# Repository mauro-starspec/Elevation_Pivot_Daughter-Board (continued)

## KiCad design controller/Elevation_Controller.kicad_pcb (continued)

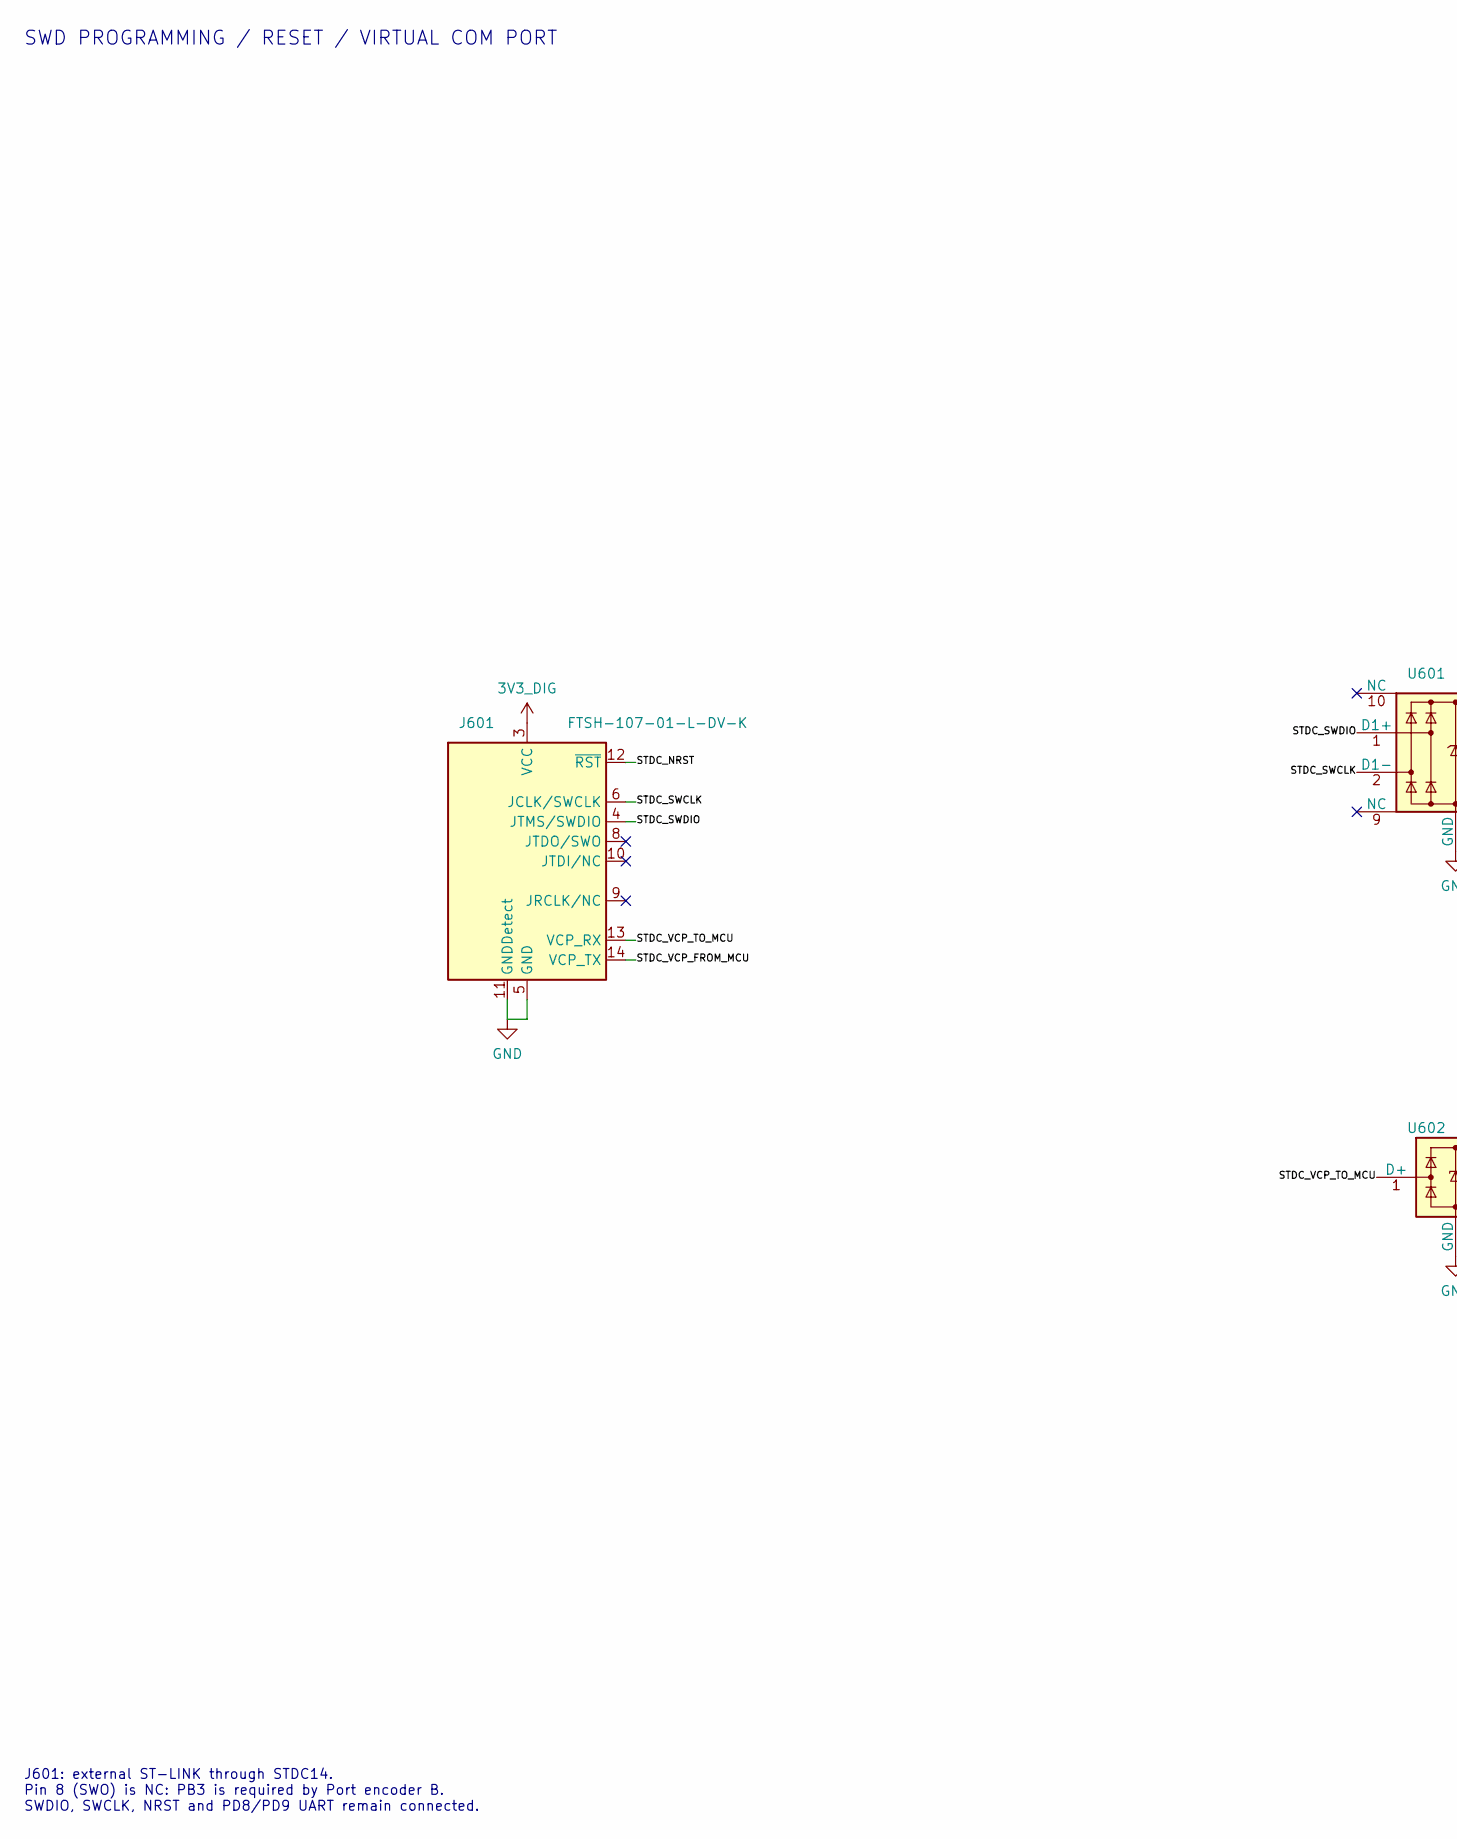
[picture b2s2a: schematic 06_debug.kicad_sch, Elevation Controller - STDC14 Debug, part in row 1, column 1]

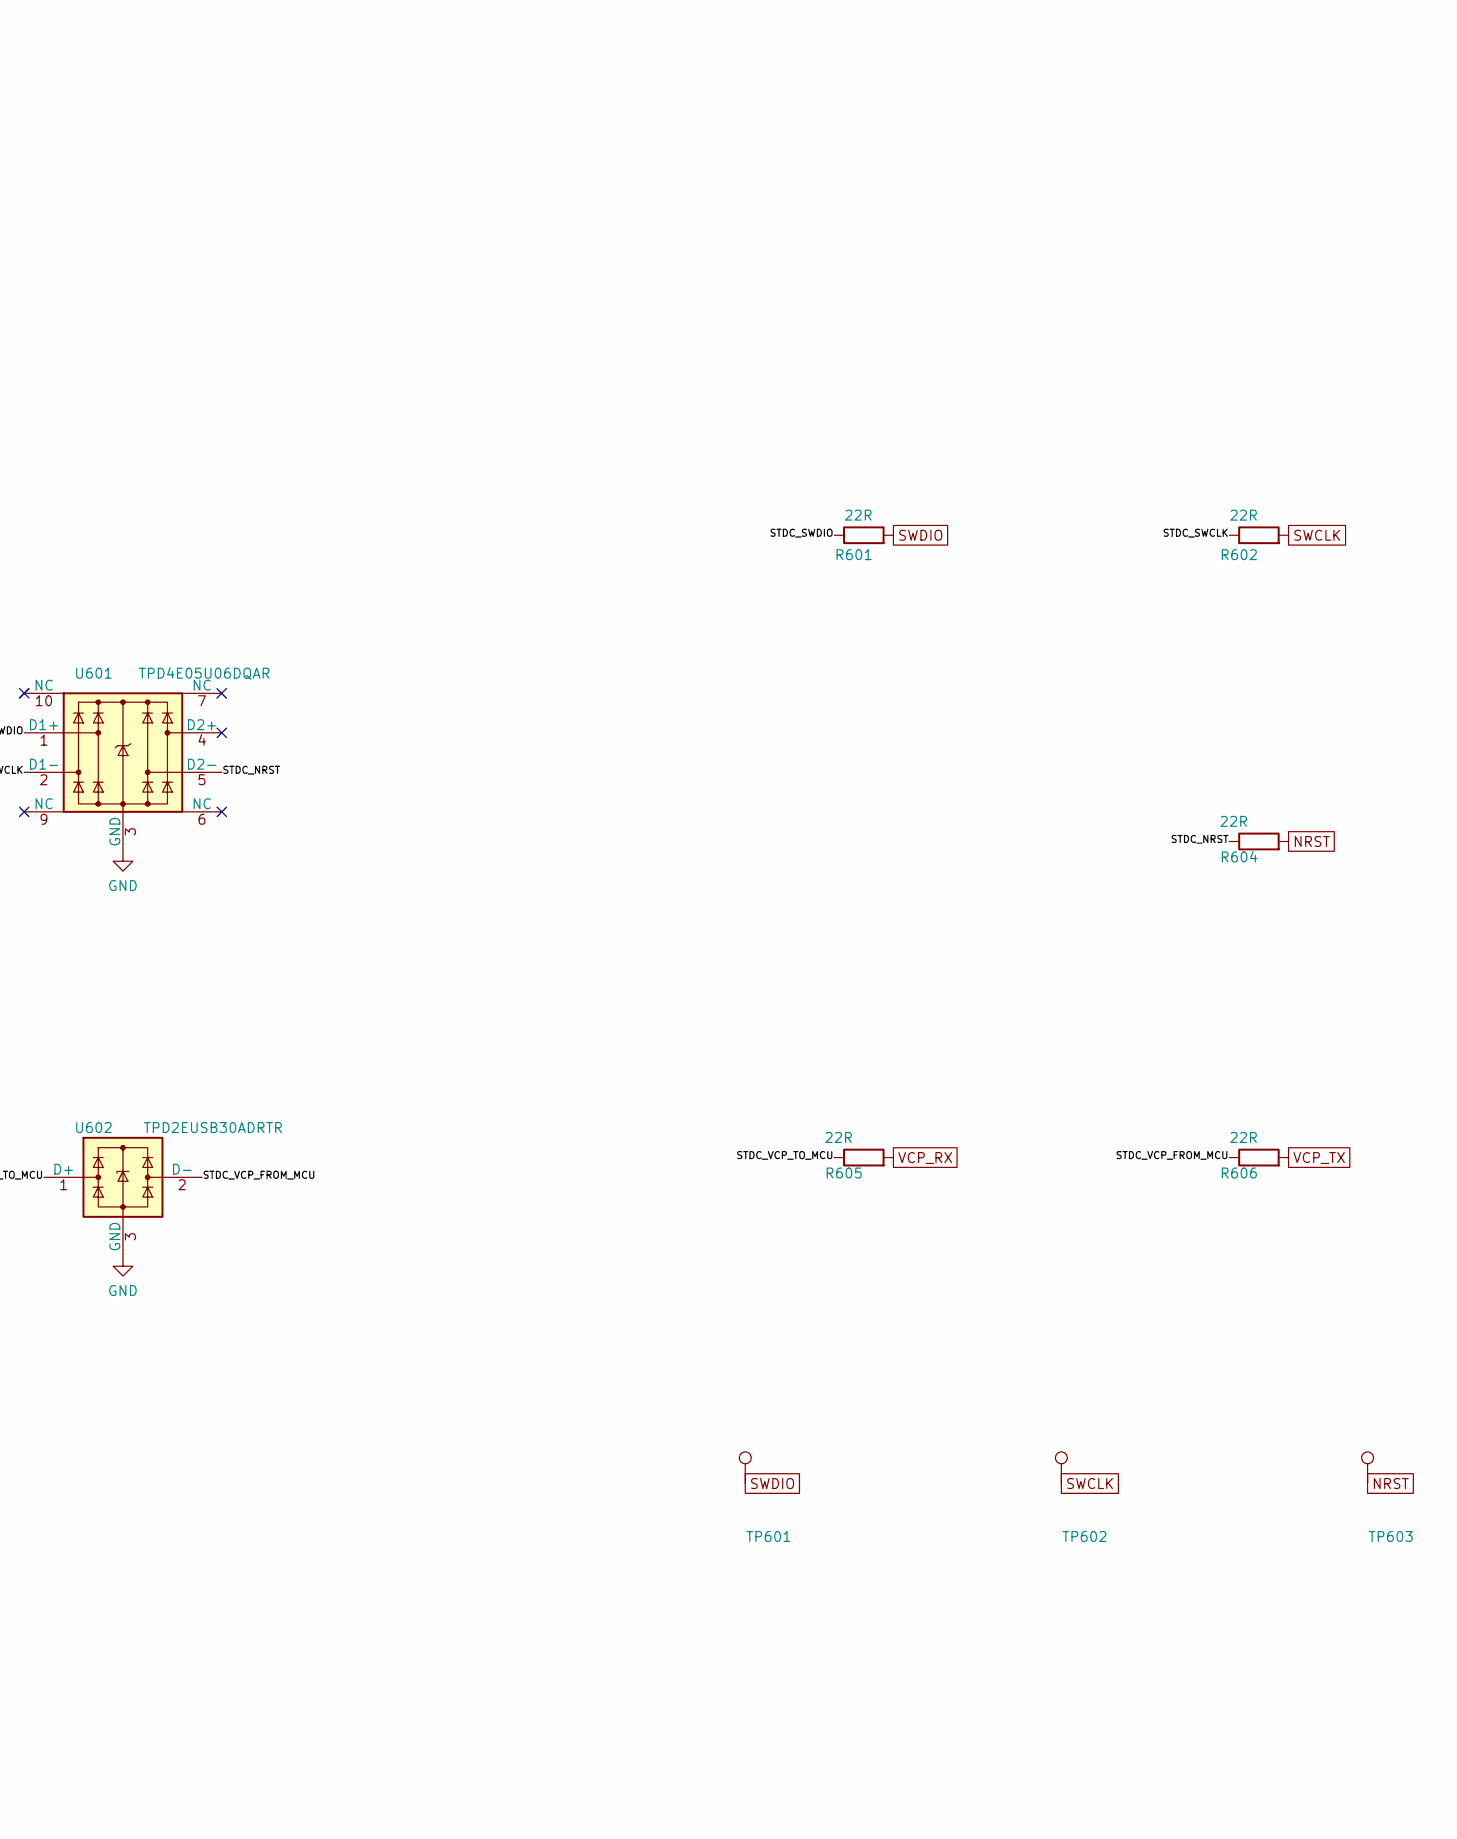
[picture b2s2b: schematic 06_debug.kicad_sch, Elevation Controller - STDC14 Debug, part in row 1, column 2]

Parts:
J601: FTSH-107-01-L-DV-K; Samtec_FTSH-107-01-L-DV-K; MPN FTSH-107-01-L-DV-K; LCSC Part # C5307809
R601, R602, R604, R605, R606: 22R; R_0805_2012Metric; MPN CRCW080522R0FKEA; LCSC Part # C844832
TP601: SWDIO; TestPoint_Pad_D2.0mm; MPN N/A; LCSC Part # N/A
TP602: SWCLK; TestPoint_Pad_D2.0mm; MPN N/A; LCSC Part # N/A
TP603: NRST; TestPoint_Pad_D2.0mm; MPN N/A; LCSC Part # N/A
U601: TPD4E05U06DQAR; USON-10_2.5x1.0mm_P0.5mm; MPN TPD4E05U06DQAR; LCSC Part # C22390021
U602: TPD2EUSB30ADRTR; Texas_DRT-3; MPN TPD2EUSB30ADRTR; LCSC Part # C94934

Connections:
3V3_DIG: J601.3 (VCC); also elsewhere on the board
/SWD and VCP/STDC_NRST: J601.12 (~RST), R604.1, U601.5 (D2-)
/SWD and VCP/STDC_SWCLK: J601.6 (JCLK/SWCLK), R602.1, U601.2 (D1-)
/SWD and VCP/STDC_SWDIO: J601.4 (JTMS/SWDIO), R601.1, U601.1 (D1+)
/SWD and VCP/STDC_VCP_FROM_MCU: J601.14 (VCP_TX), R606.1, U602.2 (D-)
/SWD and VCP/STDC_VCP_TO_MCU: J601.13 (VCP_RX), R605.1, U602.1 (D+)
GND: J601.5 (GND), J601.7 (GND), J601.11 (GNDDetect), U601.3 (GND), U601.8 (GND), U602.3 (GND); also elsewhere on the board
NRST: R604.2, TP603.1; also elsewhere on the board
SWCLK: R602.2, TP602.1; also elsewhere on the board
SWDIO: R601.2, TP601.1; also elsewhere on the board
VCP_RX: R605.2; also elsewhere on the board
VCP_TX: R606.2; also elsewhere on the board

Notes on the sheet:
J601: external ST-LINK through STDC14. Pin 8 (SWO) is NC: PB3 is required by Port encoder B. SWDIO, SWCLK, NRST and PD8/PD9 UART remain connected.
SWD PROGRAMMING / RESET / VIRTUAL COM PORT

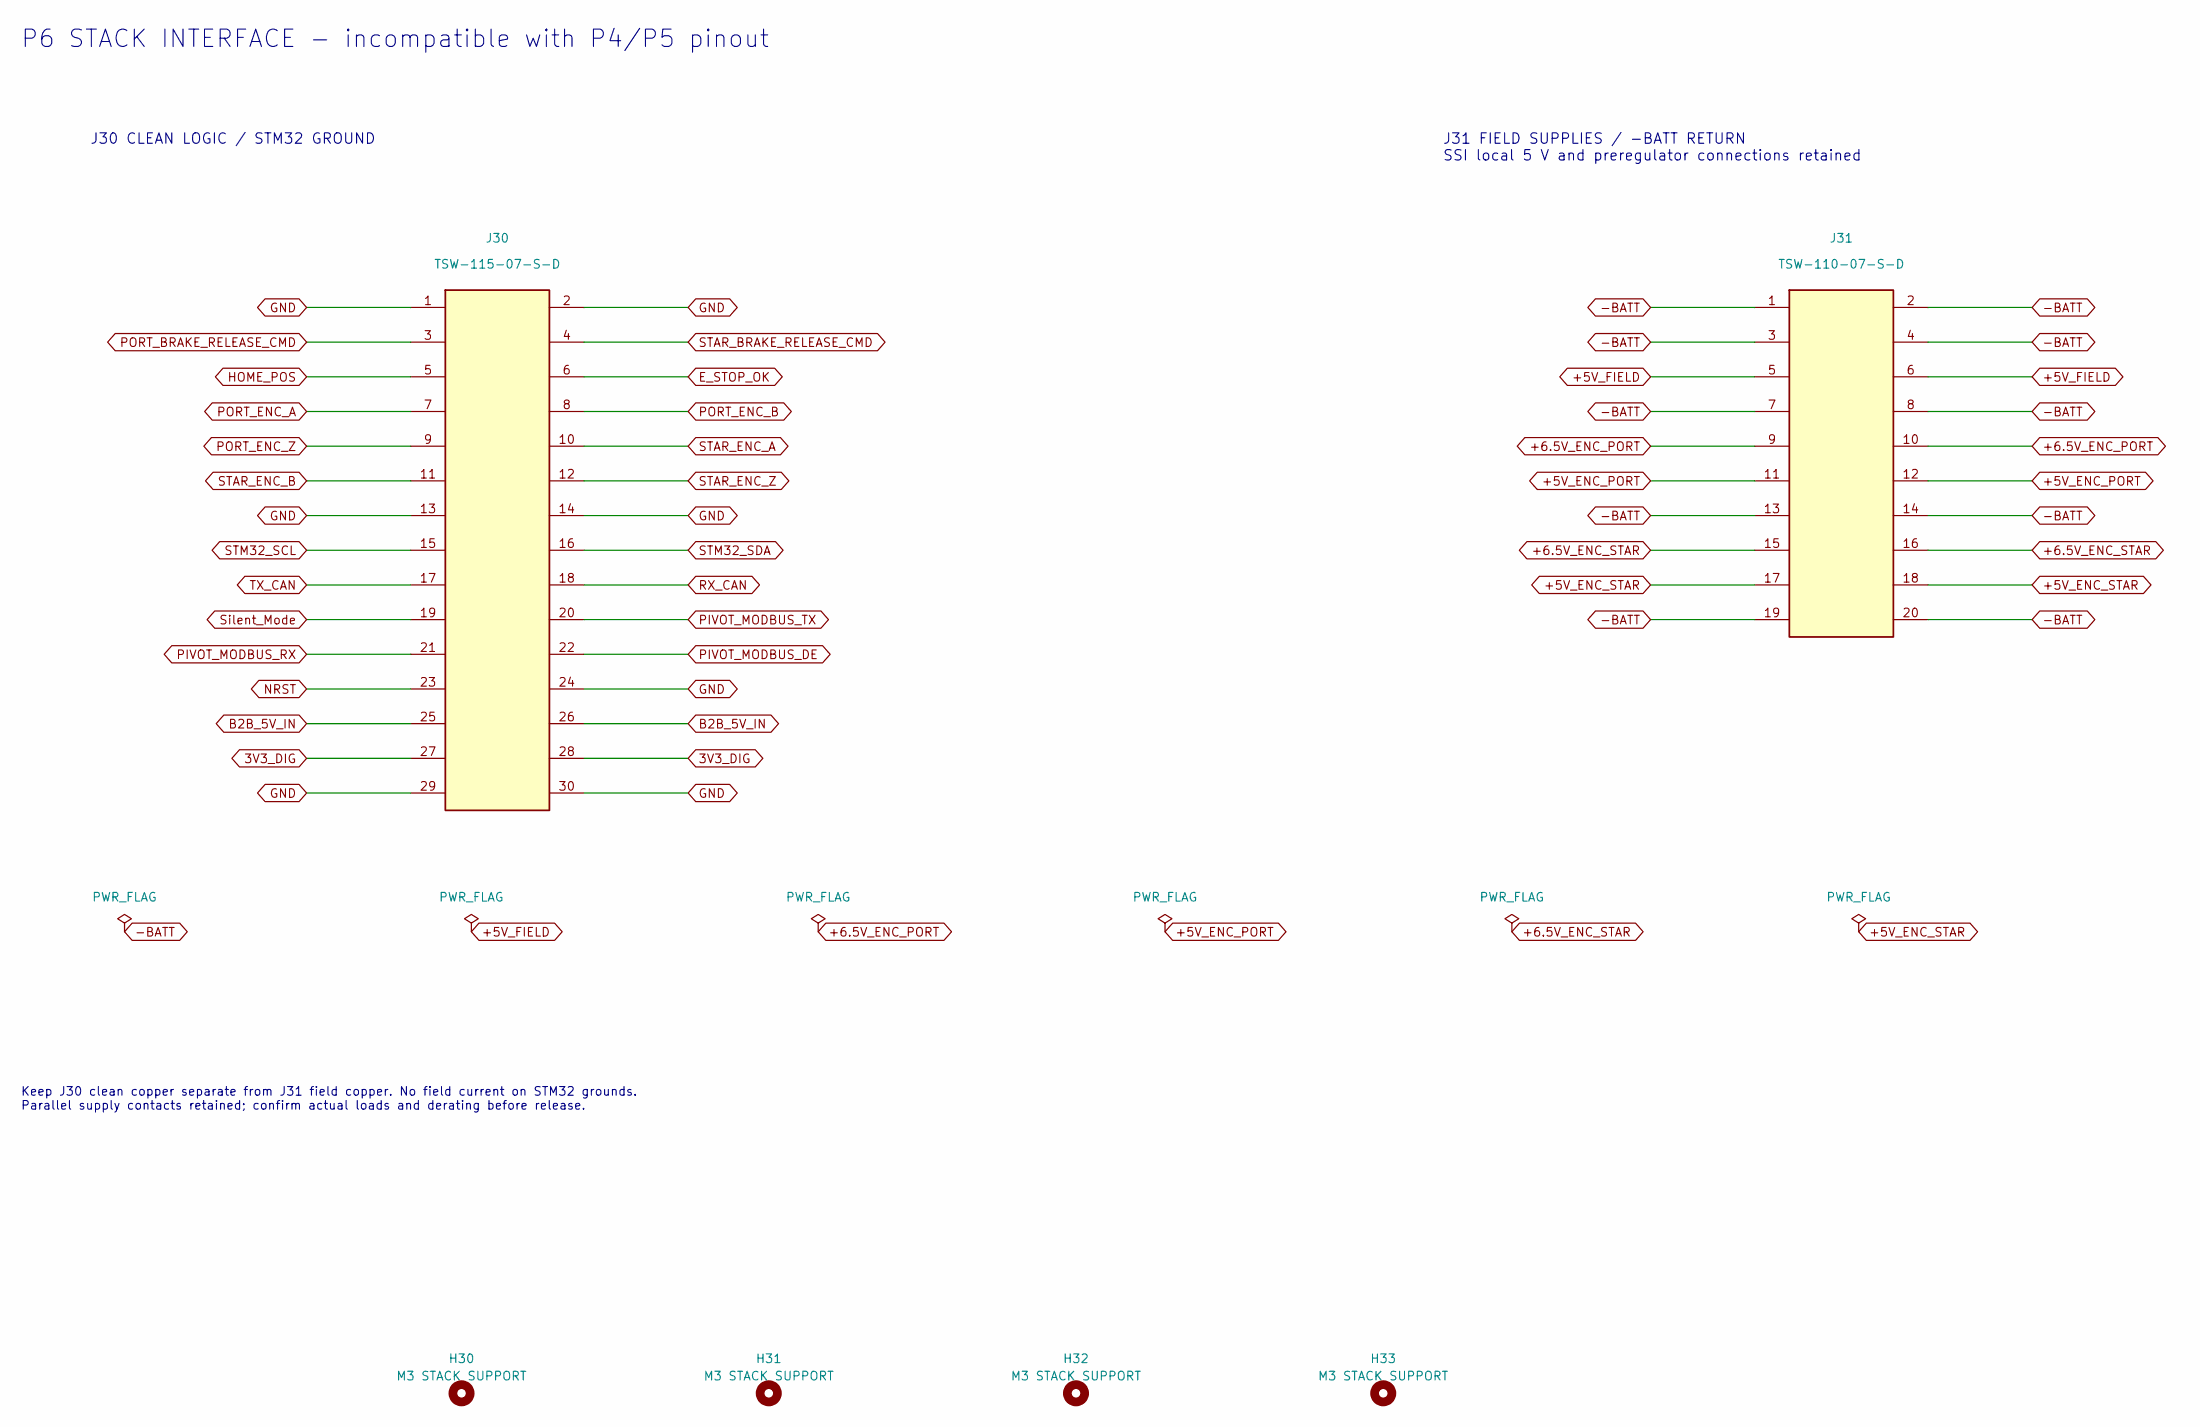
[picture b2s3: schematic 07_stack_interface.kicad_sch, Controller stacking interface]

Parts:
H30, H31, H32, H33: M3 STACK SUPPORT; MountingHole_3.2mm_M3; MPN N/A; JLCPCB Status N/A
J30: TSW-115-07-S-D; Samtec_TSW-115-07-S-D; MPN TSW-115-07-S-D; JLCPCB Status No verified JLCPCB ID; source or consign
J31: TSW-110-07-S-D; Samtec_TSW-110-07-S-D; MPN TSW-110-07-S-D; JLCPCB Status No verified JLCPCB ID; source or consign

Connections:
3V3_DIG: J30.27, J30.28; also elsewhere on the board
+5V_ENC_PORT: J31.11, J31.12; also elsewhere on the board
+5V_ENC_STAR: J31.17, J31.18; also elsewhere on the board
+5V_FIELD: J31.5, J31.6; also elsewhere on the board
+6.5V_ENC_PORT: J31.9, J31.10; also elsewhere on the board
+6.5V_ENC_STAR: J31.15, J31.16; also elsewhere on the board
-BATT: J31.1, J31.2, J31.3, J31.4, J31.7, J31.8, J31.13, J31.14, J31.19, J31.20; also elsewhere on the board
B2B_5V_IN: J30.25, J30.26; also elsewhere on the board
E_STOP_OK: J30.6; also elsewhere on the board
GND: J30.1, J30.2, J30.13, J30.14, J30.24, J30.29, J30.30; also elsewhere on the board
HOME_POS: J30.5; also elsewhere on the board
NRST: J30.23; also elsewhere on the board
PIVOT_MODBUS_DE: J30.22; also elsewhere on the board
PIVOT_MODBUS_RX: J30.21; also elsewhere on the board
PIVOT_MODBUS_TX: J30.20; also elsewhere on the board
PORT_BRAKE_RELEASE_CMD: J30.3; also elsewhere on the board
PORT_ENC_A: J30.7; also elsewhere on the board
PORT_ENC_B: J30.8; also elsewhere on the board
PORT_ENC_Z: J30.9; also elsewhere on the board
RX_CAN: J30.18; also elsewhere on the board
STAR_BRAKE_RELEASE_CMD: J30.4; also elsewhere on the board
STAR_ENC_A: J30.10; also elsewhere on the board
STAR_ENC_B: J30.11; also elsewhere on the board
STAR_ENC_Z: J30.12; also elsewhere on the board
STM32_SCL: J30.15; also elsewhere on the board
STM32_SDA: J30.16; also elsewhere on the board
Silent_Mode: J30.19; also elsewhere on the board
TX_CAN: J30.17; also elsewhere on the board

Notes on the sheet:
P6 STACK INTERFACE - incompatible with P4/P5 pinout
J30 CLEAN LOGIC / STM32 GROUND
J31 FIELD SUPPLIES / -BATT RETURN SSI local 5 V and preregulator connections retained
Keep J30 clean copper separate from J31 field copper. No field current on STM32 grounds. Parallel supply contacts retained; confirm actual loads and derating before release.

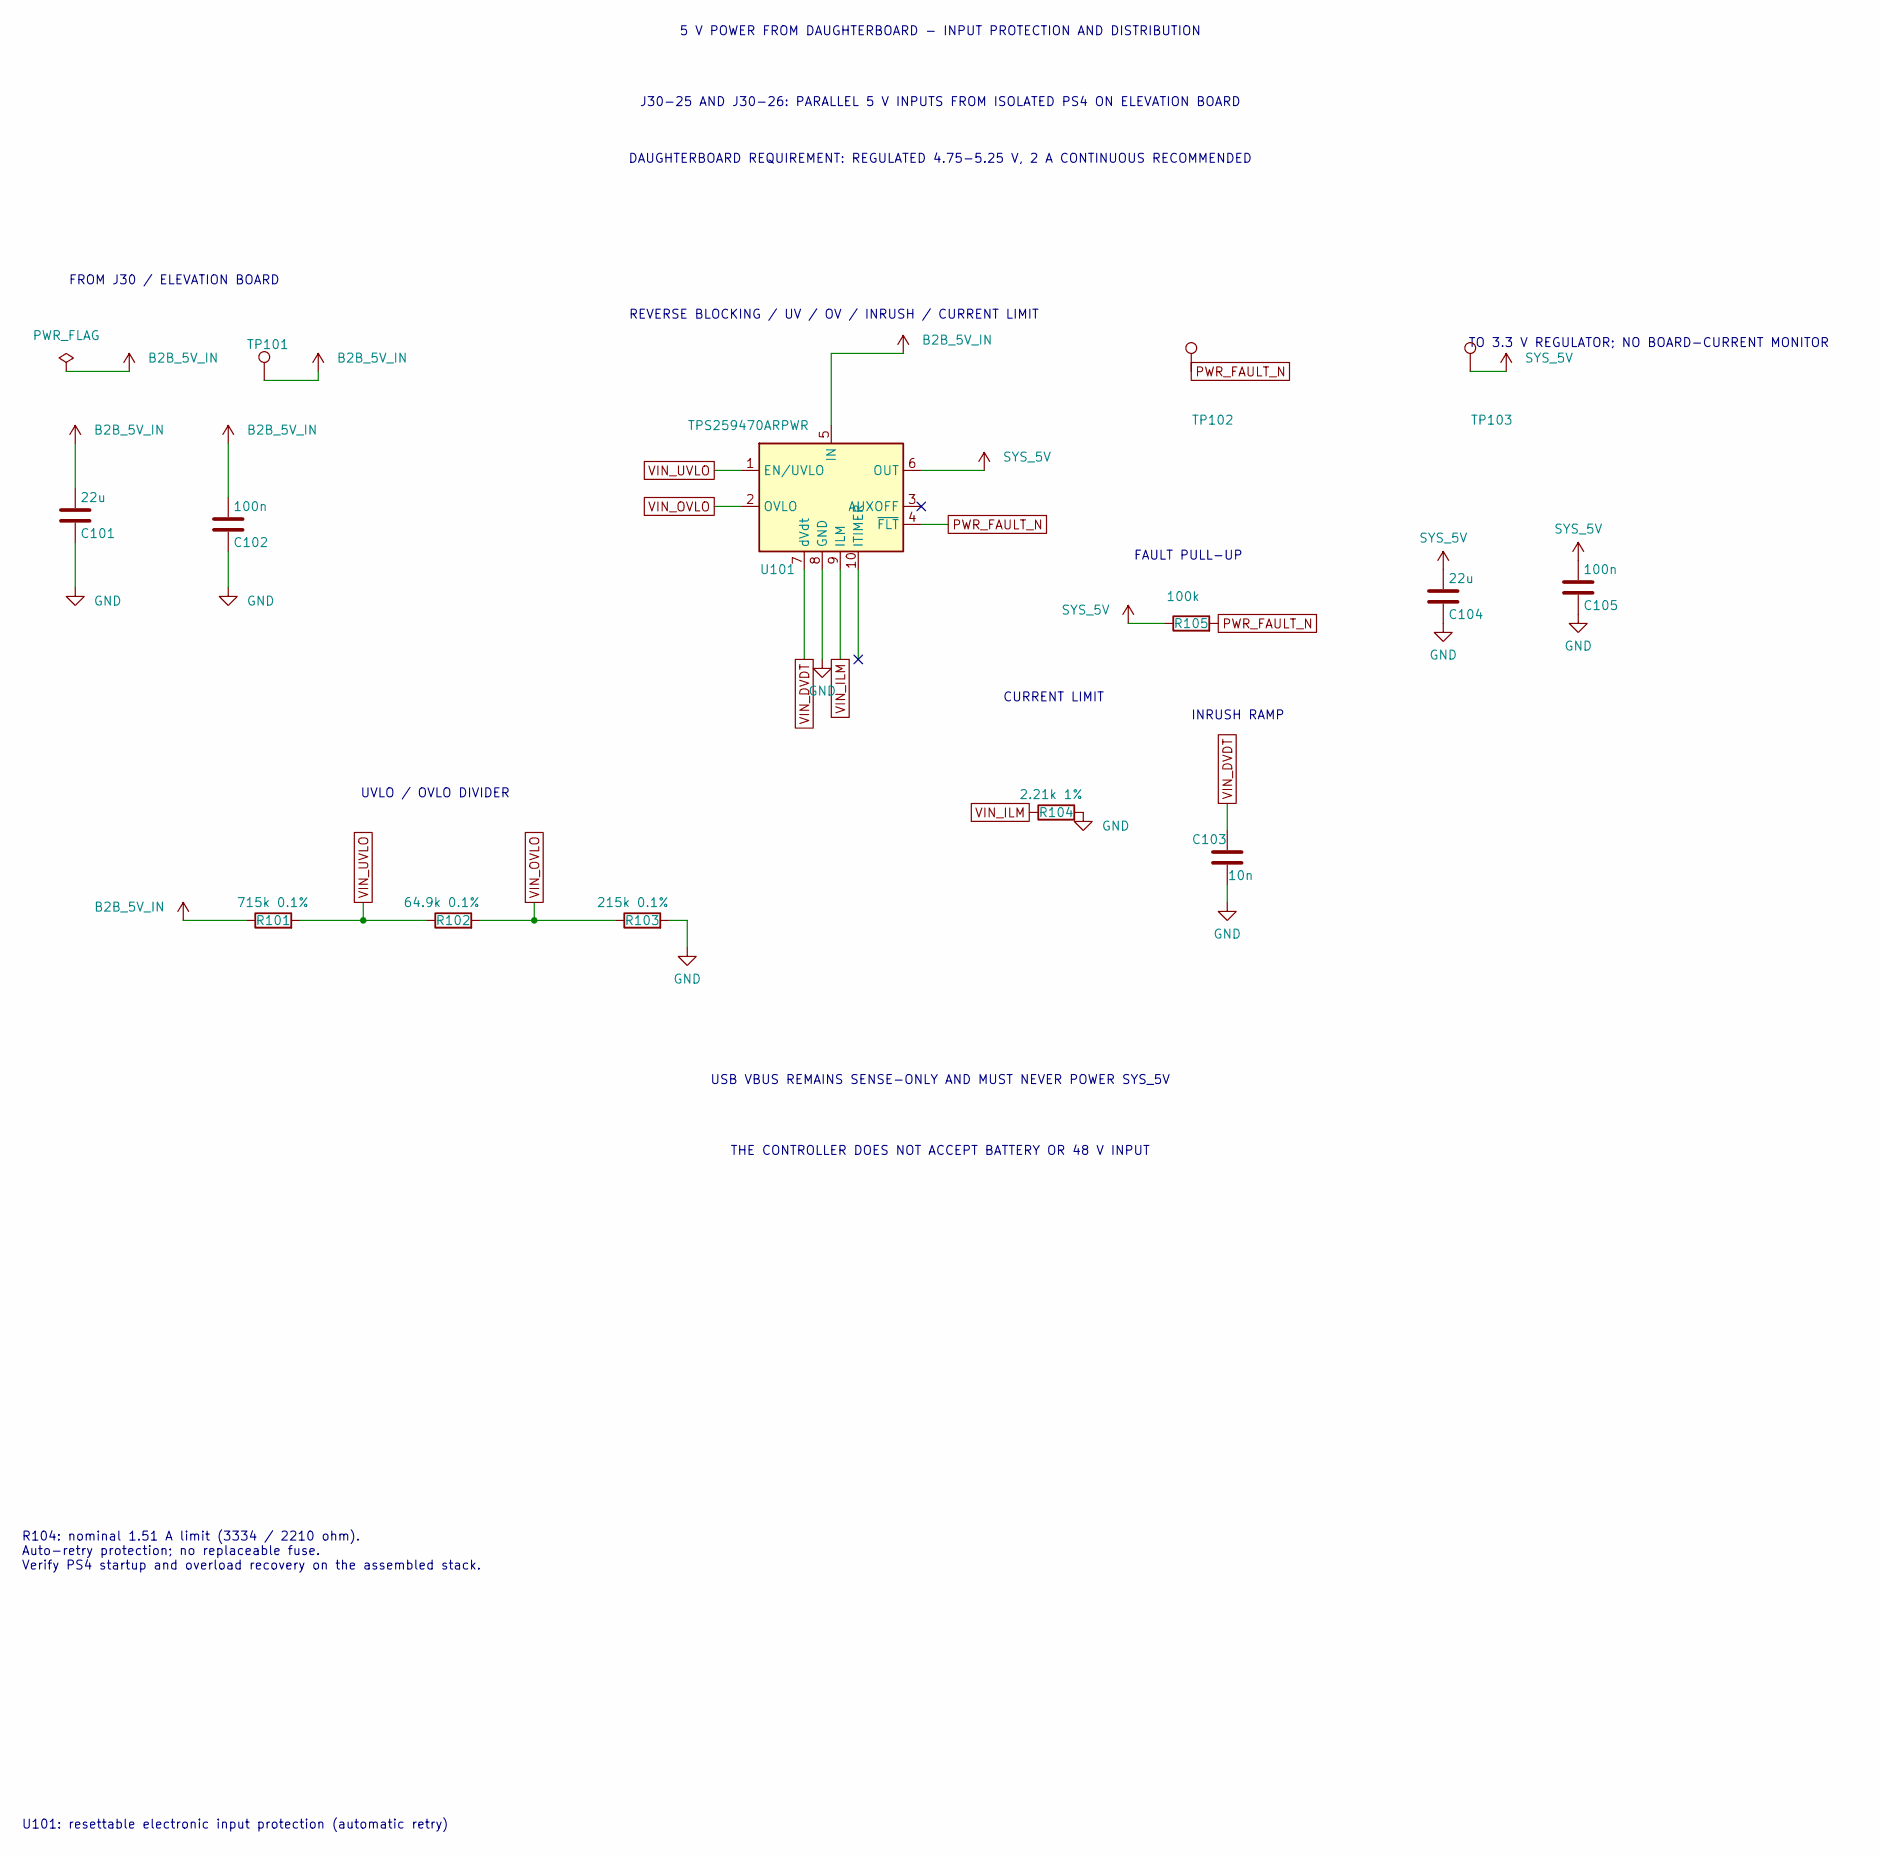
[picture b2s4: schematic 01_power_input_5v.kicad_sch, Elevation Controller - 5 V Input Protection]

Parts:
C101, C104: 22u; C_1210_3225Metric; Voltage 25V; MPN C1210C226K3RACTU; LCSC Part # C22411650
C102, C105: 100n; C_0805_2012Metric; Voltage 50V; MPN C0805C104K5RACTU; LCSC Part # C3018562
C103: 10n; C_0805_2012Metric; Voltage 50V; MPN C0805C103K5RACTU; LCSC Part # C2167345
R101: 715k 0.1%; R_0805_2012Metric; MPN TNPW0805715KBEEA; LCSC Part # NOT_LISTED
R102: 64.9k 0.1%; R_0805_2012Metric; MPN TNPW080564K9BEEA; LCSC Part # NOT_LISTED
R103: 215k 0.1%; R_0805_2012Metric; MPN TNPW0805215KBEEA; LCSC Part # NOT_LISTED
R104: 2.21k 1%; R_0805_2012Metric; MPN CRCW08052K21FKEA; JLCPCB Status No verified JLCPCB ID; source or consign
R105: 100k; R_0805_2012Metric; MPN CRCW0805100KFKEA; LCSC Part # C844935
TP101: B2B_5V_IN; TestPoint_Pad_D2.0mm; MPN N/A; LCSC Part # N/A
TP102: PWR_FAULT_N; TestPoint_Pad_D2.0mm; MPN N/A; LCSC Part # N/A
TP103: SYS_5V; TestPoint_Pad_D2.0mm; MPN N/A; LCSC Part # N/A
U101: TPS259470ARPWR; TI_RPW0010A_VQFN-HR-10_2x2mm_P0.475mm; MPN TPS259470ARPWR; LCSC Part # C3662799

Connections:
B2B_5V_IN: C101.1, C102.1, R101.1, TP101.1, U101.5 (IN); also elsewhere on the board
GND: C101.2, C102.2, C103.2, C104.2, C105.2, R103.2, R104.2, U101.8 (GND); also elsewhere on the board
PWR_FAULT_N: R105.2, TP102.1, U101.4 (~FLT)
SYS_5V: C104.1, C105.1, R105.1, TP103.1, U101.6 (OUT); also elsewhere on the board
VIN_DVDT: C103.1, U101.7 (dVdt)
VIN_ILM: R104.1, U101.9 (ILM)
VIN_OVLO: R102.2, R103.1, U101.2 (OVLO)
VIN_UVLO: R101.2, R102.1, U101.1 (EN/UVLO)

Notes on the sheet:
CURRENT LIMIT
USB VBUS REMAINS SENSE-ONLY AND MUST NEVER POWER SYS_5V
R104: nominal 1.51 A limit (3334 / 2210 ohm). Auto-retry protection; no replaceable fuse. Verify PS4 startup and overload recovery on the assembled stack.
5 V POWER FROM DAUGHTERBOARD - INPUT PROTECTION AND DISTRIBUTION
UVLO / OVLO DIVIDER
REVERSE BLOCKING / UV / OV / INRUSH / CURRENT LIMIT
J30-25 AND J30-26: PARALLEL 5 V INPUTS FROM ISOLATED PS4 ON ELEVATION BOARD
FROM J30 / ELEVATION BOARD
INRUSH RAMP
U101: resettable electronic input protection (automatic retry)
DAUGHTERBOARD REQUIREMENT: REGULATED 4.75-5.25 V, 2 A CONTINUOUS RECOMMENDED
TO 3.3 V REGULATOR; NO BOARD-CURRENT MONITOR
THE CONTROLLER DOES NOT ACCEPT BATTERY OR 48 V INPUT
FAULT PULL-UP

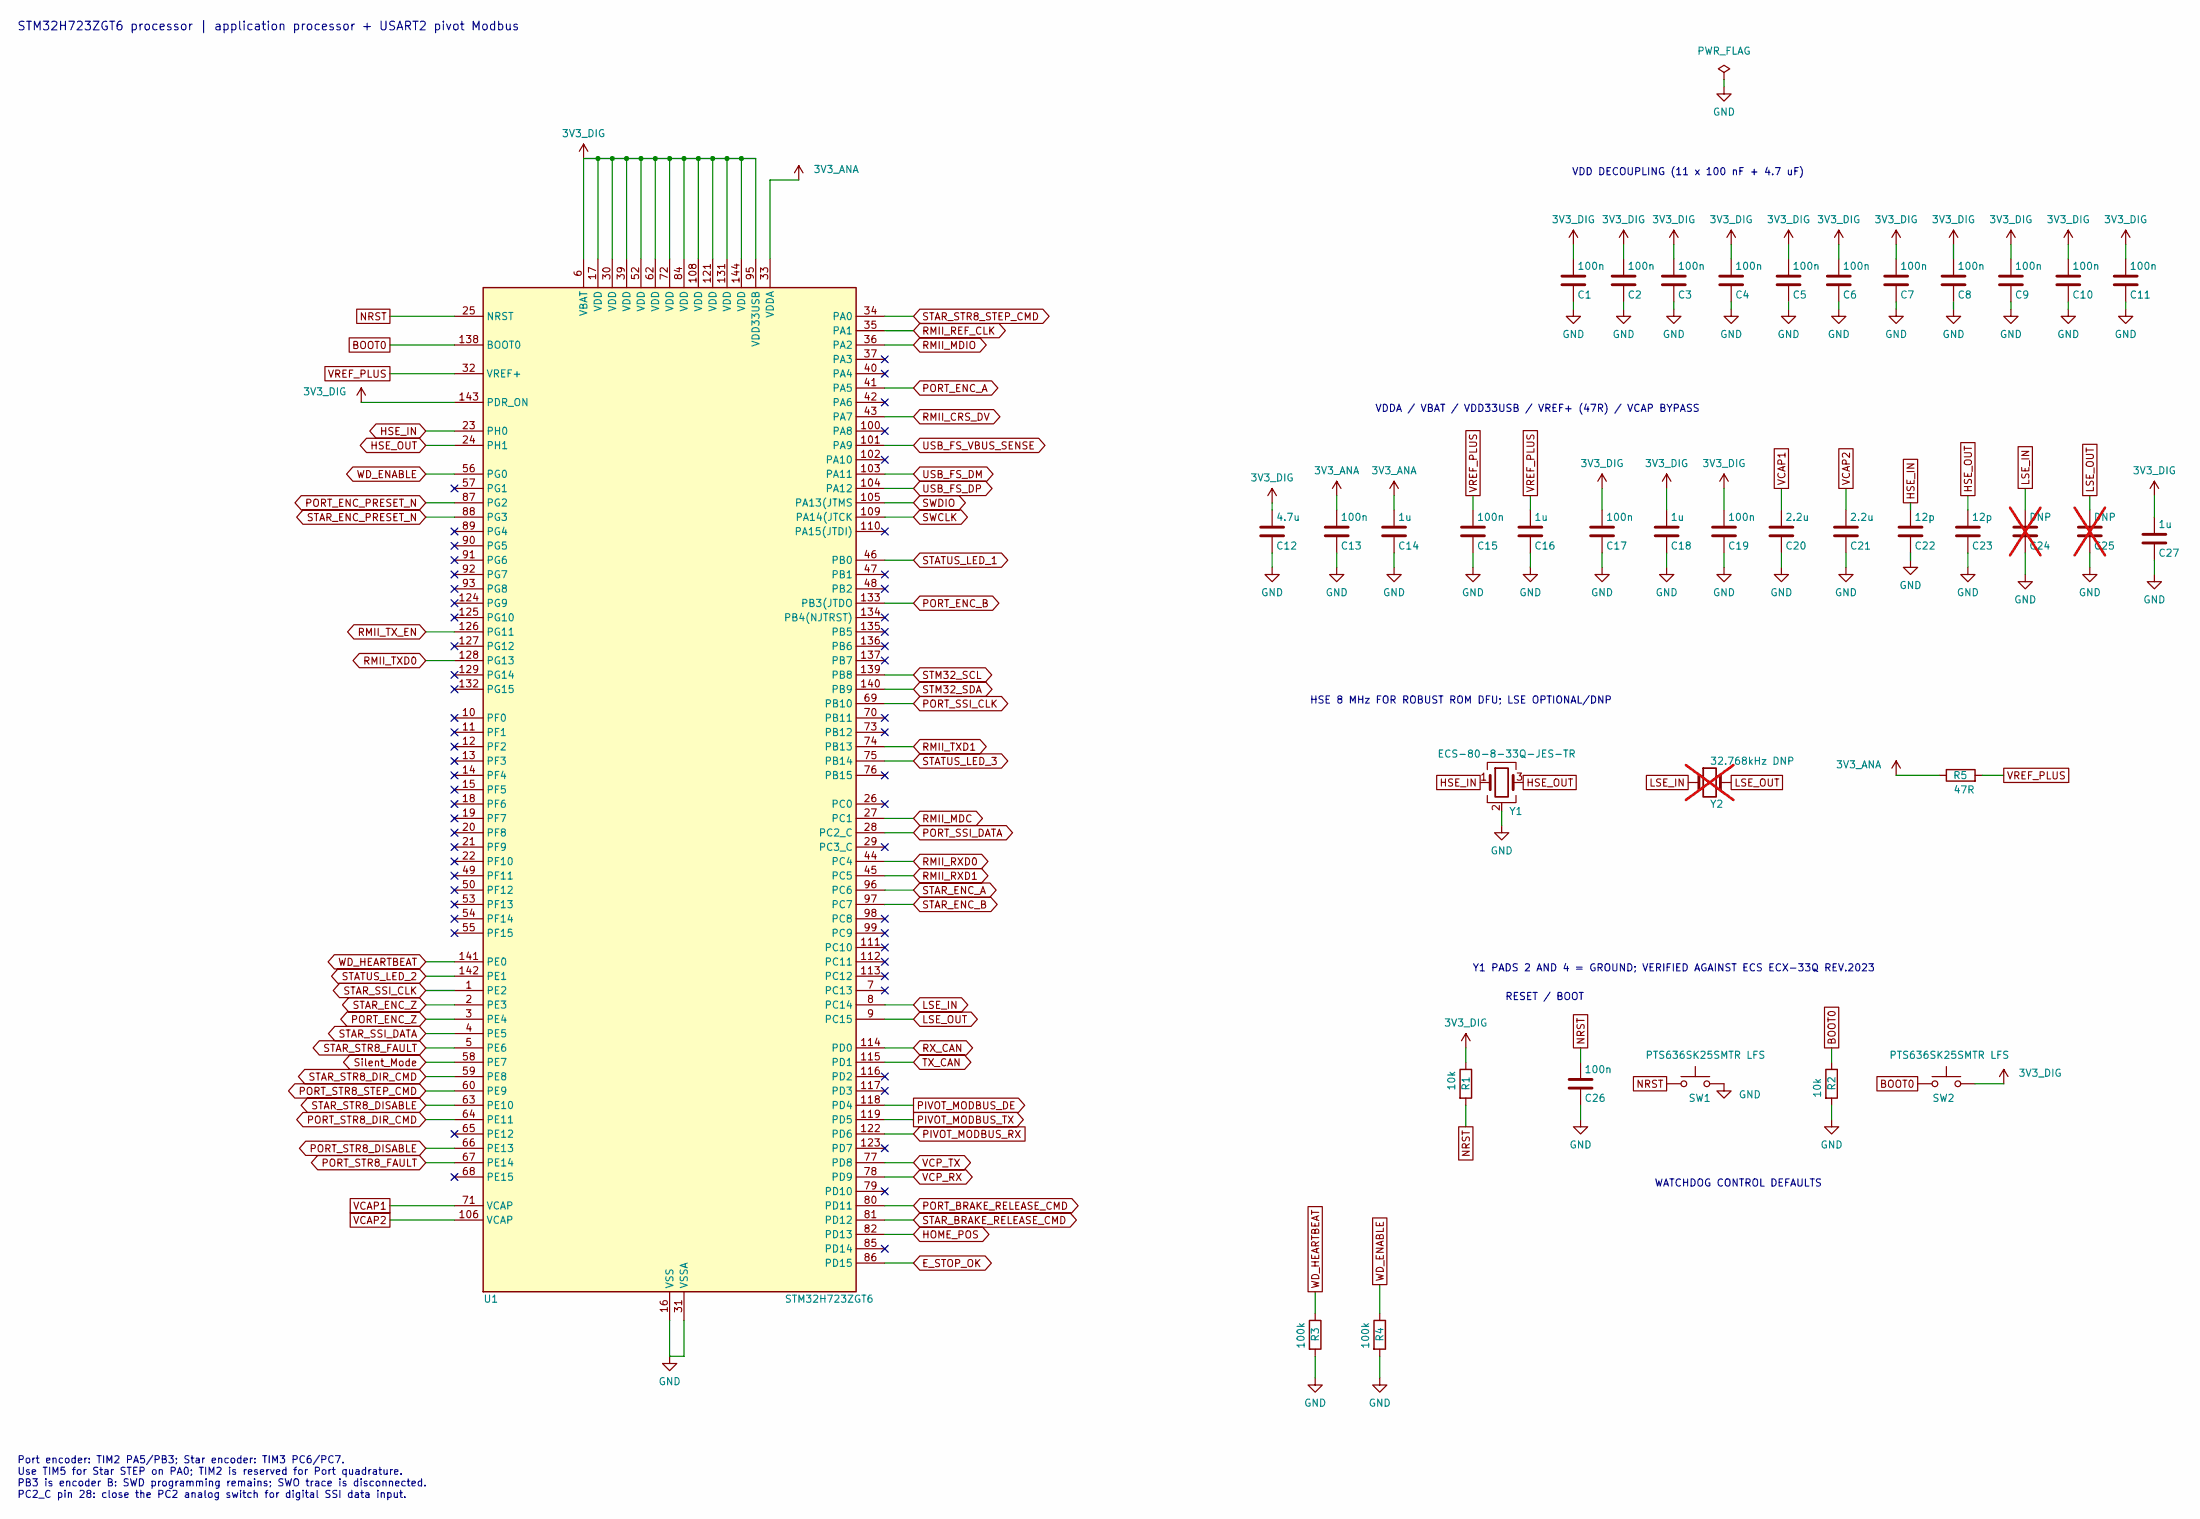
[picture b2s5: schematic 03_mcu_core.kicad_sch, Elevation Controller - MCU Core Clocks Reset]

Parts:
C1, C2, C3, C4, C5, C6, C7, C8, C9, C10, C11, C13, C15, C17, C19, C26: 100n; C_0805_2012Metric; Voltage 50V; MPN C0805C104K5RACTU; LCSC Part # C3018562
C12: 4.7u; C_0805_2012Metric; Voltage 25V; MPN C2012X7R1E475K125AB; LCSC Part # NOT_LISTED
C14, C16, C18, C27: 1u; C_0805_2012Metric; Voltage 25V; MPN C2012X7R1E105K085AB; LCSC Part # NOT_LISTED
C20, C21: 2.2u; C_0805_2012Metric; Voltage 25V; MPN C2012X7R1E225K125AB; LCSC Part # NOT_LISTED
C22, C23: 12p; C_0805_2012Metric; Voltage 50V; MPN C0805C120J5GACTU; LCSC Part # C2168859
C24, C25: DNP; C_0805_2012Metric; MPN NOT SELECTED - DNP; LCSC Part # NOT_SELECTED; not fitted
R1, R2: 10k; R_0805_2012Metric; MPN CRCW080510K0FKEA; LCSC Part # C844937
R3, R4: 100k; R_0805_2012Metric; MPN CRCW0805100KFKEA; LCSC Part # C844935
R5: 47R; R_0805_2012Metric; MPN CRCW080547R0FKEA; LCSC Part # C844845
SW1, SW2: PTS636SK25SMTR LFS; SW_Tactile_SPST_NO_Straight_CK_PTS636Sx25SMTRLFS; MPN PTS636SK25SMTR LFS; LCSC Part # NOT_LISTED
U1: STM32H723ZGT6; LQFP-144_20x20mm_P0.5mm; MPN STM32H723ZGT6; LCSC Part # C730146
Y1: ECS-80-8-33Q-JES-TR; Crystal_SMD_3225-4Pin_3.2x2.5mm; MPN ECS-80-8-33Q-JES-TR; LCSC Part # C5727442
Y2: 32.768kHz DNP; Crystal_SMD_3225-4Pin_3.2x2.5mm; MPN NOT SELECTED - DNP; LCSC Part # NOT_SELECTED; not fitted

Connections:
3V3_ANA: C13.1, C14.1, R5.1, U1.33 (VDDA); also elsewhere on the board
3V3_DIG: C1.1, C2.1, C3.1, C4.1, C5.1, C6.1, C7.1, C8.1, C9.1, C10.1, C11.1, C12.1, C17.1, C18.1, C19.1, C27.1, R1.1, SW2.2, U1.6 (VBAT), U1.17 (VDD), U1.30 (VDD), U1.39 (VDD), U1.52 (VDD), U1.62 (VDD), U1.72 (VDD), U1.84 (VDD), U1.95 (VDD33USB), U1.108 (VDD), U1.121 (VDD), U1.131 (VDD), U1.143 (PDR_ON), U1.144 (VDD); also elsewhere on the board
BOOT0: R2.1, SW2.1, U1.138 (BOOT0)
E_STOP_OK: U1.86 (PD15); also elsewhere on the board
GND: C1.2, C2.2, C3.2, C4.2, C5.2, C6.2, C7.2, C8.2, C9.2, C10.2, C11.2, C12.2, C13.2, C14.2, C15.2, C16.2, C17.2, C18.2, C19.2, C20.2, C21.2, C22.2, C23.2, C24.2, C25.2, C26.2, C27.2, R2.2, R3.2, R4.2, SW1.2, U1.16 (VSS), U1.31 (VSSA), U1.38 (VSS), U1.51 (VSS), U1.61 (VSS), U1.83 (VSS), U1.94 (VSS), U1.107 (VSS), U1.120 (VSS), U1.130 (VSS), Y1.2 (G), Y1.4 (G); also elsewhere on the board
HOME_POS: U1.82 (PD13); also elsewhere on the board
HSE_IN: C22.1, U1.23 (PH0), Y1.1
HSE_OUT: C23.1, U1.24 (PH1), Y1.3
LSE_IN: C24.1, U1.8 (PC14), Y2.1
LSE_OUT: C25.1, U1.9 (PC15), Y2.2
NRST: C26.1, R1.2, SW1.1, U1.25 (NRST); also elsewhere on the board
PIVOT_MODBUS_DE: U1.118 (PD4); also elsewhere on the board
PIVOT_MODBUS_RX: U1.122 (PD6); also elsewhere on the board
PIVOT_MODBUS_TX: U1.119 (PD5); also elsewhere on the board
PORT_BRAKE_RELEASE_CMD: U1.80 (PD11); also elsewhere on the board
PORT_ENC_A: U1.41 (PA5); also elsewhere on the board
PORT_ENC_B: U1.133 (PB3(JTDO); also elsewhere on the board
PORT_ENC_PRESET_N: U1.87 (PG2); also elsewhere on the board
PORT_ENC_Z: U1.3 (PE4); also elsewhere on the board
PORT_SSI_CLK: U1.69 (PB10); also elsewhere on the board
PORT_SSI_DATA: U1.28 (PC2_C); also elsewhere on the board
PORT_STR8_DIR_CMD: U1.64 (PE11); also elsewhere on the board
PORT_STR8_DISABLE: U1.66 (PE13); also elsewhere on the board
PORT_STR8_FAULT: U1.67 (PE14); also elsewhere on the board
PORT_STR8_STEP_CMD: U1.60 (PE9); also elsewhere on the board
RMII_CRS_DV: U1.43 (PA7); also elsewhere on the board
RMII_MDC: U1.27 (PC1); also elsewhere on the board
RMII_MDIO: U1.36 (PA2); also elsewhere on the board
RMII_REF_CLK: U1.35 (PA1); also elsewhere on the board
RMII_RXD0: U1.44 (PC4); also elsewhere on the board
RMII_RXD1: U1.45 (PC5); also elsewhere on the board
RMII_TXD0: U1.128 (PG13); also elsewhere on the board
RMII_TXD1: U1.74 (PB13); also elsewhere on the board
RMII_TX_EN: U1.126 (PG11); also elsewhere on the board
RX_CAN: U1.114 (PD0); also elsewhere on the board
STAR_BRAKE_RELEASE_CMD: U1.81 (PD12); also elsewhere on the board
STAR_ENC_A: U1.96 (PC6); also elsewhere on the board
STAR_ENC_B: U1.97 (PC7); also elsewhere on the board
STAR_ENC_PRESET_N: U1.88 (PG3); also elsewhere on the board
STAR_ENC_Z: U1.2 (PE3); also elsewhere on the board
STAR_SSI_CLK: U1.1 (PE2); also elsewhere on the board
STAR_SSI_DATA: U1.4 (PE5); also elsewhere on the board
STAR_STR8_DIR_CMD: U1.59 (PE8); also elsewhere on the board
STAR_STR8_DISABLE: U1.63 (PE10); also elsewhere on the board
STAR_STR8_FAULT: U1.5 (PE6); also elsewhere on the board
STAR_STR8_STEP_CMD: U1.34 (PA0); also elsewhere on the board
STATUS_LED_1: U1.46 (PB0); also elsewhere on the board
STATUS_LED_2: U1.142 (PE1); also elsewhere on the board
STATUS_LED_3: U1.75 (PB14); also elsewhere on the board
STM32_SCL: U1.139 (PB8); also elsewhere on the board
STM32_SDA: U1.140 (PB9); also elsewhere on the board
SWCLK: U1.109 (PA14(JTCK); also elsewhere on the board
SWDIO: U1.105 (PA13(JTMS); also elsewhere on the board
Silent_Mode: U1.58 (PE7); also elsewhere on the board
TX_CAN: U1.115 (PD1); also elsewhere on the board
USB_FS_DM: U1.103 (PA11); also elsewhere on the board
USB_FS_DP: U1.104 (PA12); also elsewhere on the board
USB_FS_VBUS_SENSE: U1.101 (PA9); also elsewhere on the board
VCAP1: C20.1, U1.71 (VCAP)
VCAP2: C21.1, U1.106 (VCAP)
VCP_RX: U1.78 (PD9); also elsewhere on the board
VCP_TX: U1.77 (PD8); also elsewhere on the board
VREF_PLUS: C15.1, C16.1, R5.2, U1.32 (VREF+)
WD_ENABLE: R4.1, U1.56 (PG0); also elsewhere on the board
WD_HEARTBEAT: R3.1, U1.141 (PE0); also elsewhere on the board

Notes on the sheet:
RESET / BOOT
Port encoder: TIM2 PA5/PB3; Star encoder: TIM3 PC6/PC7. Use TIM5 for Star STEP on PA0; TIM2 is reserved for Port quadrature. PB3 is encoder B: SWD programming remains; SWO trace is disconnected. PC2_C pin 28: close the PC2 analog switch for digital SSI data input.
Y1 PADS 2 AND 4 = GROUND; VERIFIED AGAINST ECS ECX-33Q REV.2023
VDDA / VBAT / VDD33USB / VREF+ (47R) / VCAP BYPASS
HSE 8 MHz FOR ROBUST ROM DFU; LSE OPTIONAL/DNP
WATCHDOG CONTROL DEFAULTS
VDD DECOUPLING (11 x 100 nF + 4.7 uF)
STM32H723ZGT6 processor | application processor + USART2 pivot Modbus

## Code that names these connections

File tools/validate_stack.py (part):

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        report['pre_modbus_net_groups_preserved'][name] = preserve_groups(old['nets'], nets, preserved_pins)

    # End-to-end UART, reset behavior, bus polarity, power/isolation and cable.
    for contact, pad, signal, ic_pin in [('13','119','PIVOT_MODBUS_TX','6'),
            ('14','122','PIVOT_MODBUS_RX','3'), ('18','118','PIVOT_MODBUS_DE','5')]:
        assert cp[('U1',pad)] == cp[('J31',contact)] == signal
        assert ep[('U160',ic_pin)] == ep[('J31',contact)]
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    for ref, numbers in [('U160',['7','10','11','14']),('J22',['2','3','4','6','7','8'])]:
        inst=instance(mb,ref); pin_positions=pins(library(mb,inst),inst)
        for number in numbers: assert pin_positions[number] in nc_positions_mb, (ref,number)
    report['modbus'] = {'uart':'USART2 / AF7','tx':'PD5 / pad 119','rx':'PD6 / pad 122',
        'de':'PD4 / pad 118','transceiver':'ISO1410DWR','connector':'J22: 1=Common, 5=D1(+), 9=D0(-)',
        'new_components':len(modbus_refs),'remaining_stack_ground_contacts':13}

    # Remaining independent anchors protect field polarity, temperature and isolation.
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    assert cp[('U1','33')] == cp[('FB201','2')] == '3V3_ANA'
    assert cp[('FB201','1')] == '3V3_DIG'
    assert cp[('J31','19')] == cp[('U1','25')] == 'NRST'
    assert cp[('U1','133')] == 'PORT_ENC_B'  # PB3 must not drive SWO.
    assert 'R603' not in cc
    assert cc['R104']['value'] == '2.21k 1%'
    assert 'INA181' not in ' '.join(c['value'] for c in cc.values())
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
